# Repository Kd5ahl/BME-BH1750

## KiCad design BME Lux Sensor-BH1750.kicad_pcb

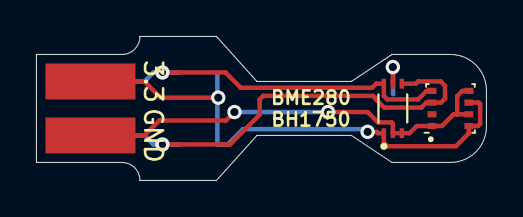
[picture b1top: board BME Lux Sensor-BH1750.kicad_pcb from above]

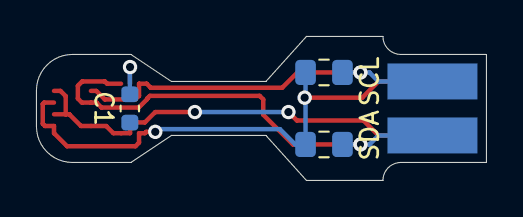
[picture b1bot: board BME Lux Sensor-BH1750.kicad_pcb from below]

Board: 2 copper layers, 25.0 x 8.0 mm, 9 parts (5 on the bottom side), 5 nets.

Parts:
C1: 1uF; C_0603_1608Metric
R1, R2: 4.7K; R_0805_2012Metric_Pad1.15x1.40mm_HandSolder
TP1: SDA; 2x5 SMD Pad
TP2: SCL; 2x5 SMD Pad
TP3: 3.3; 2x5 SMD Pad
TP4: GND; 2x5 SMD Pad
U1: BME280; Bosch_LGA-8_2.5x2.5mm_P0.65mm_ClockwisePinNumbering
U2: BH1750FVI-TR; XDCR_BH1750FVI-TR

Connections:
3.3: R1.1, R2.1, TP3.1, U1.6, U1.8, U2.1
GND: C1.1, TP4.1, U1.1, U1.5, U1.7, U2.2, U2.3
unnamed: C1.2, U2.5
SCL: R2.2, TP2.1, U1.4, U2.6
SDA: R1.2, TP1.1, U1.3, U2.4
